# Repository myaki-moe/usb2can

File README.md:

# USB2CAN

USB2CAN is a compact and low cost open source USB to CAN bus adaptor. 

Based on candleLight firmware and STM32F072 crystal-less MCU, usb2can provides linux native socketcan support.

USB2CAN是一款紧凑且低成本的开源USB到CAN总线转化器.

基于candleLight固件和STM32F072无外置晶振MCU, usb2can提供了Linux原生SocketCAN支持.

## Quick Start | 快速开始

1. PCB proofing using GERBER file `usb2can_pcb/gerber/`
2. SMD or hand soldering using [ibom](usb2can_pcb/bom/ibom.html)
3. Build candleLight firmware
4. Flash the firmware using `dfu-utils`
5. Testing
```bash
sudo ip link set can0 up type can bitrate 1000000
# CAN receive
candump can0
# CAN send
cansend can0 200#5A5A5A5A5A5A5A5A
```

1. 使用GERBER文件 `usb2can_pcb/gerber/` 打样PCB
2. SMT或使用 [ibom](usb2can_pcb/bom/ibom.html)手工焊接
3. 编译candleLight固件
4. 使用 `dfu-utils` 烧录固件
5. 测试
```bash
sudo ip link set can0 up type can bitrate 1000000
# CAN receive
candump can0
# CAN send
cansend can0 200#5A5A5A5A5A5A5A5A
```

## Toolchains | 工具链

* PCB Design: KiCad 6.0.9
* Complier: arm-none-eabi-gcc 12.2.0
* Firmware Programmer: dfu-utils 0.11

* PCB设计: KiCad 6.0.9
* 编译器: arm-none-eabi-gcc 12.2.0
* 固件烧录: dfu-utils 0.11

## License | 许可证

* The USB2CAN project is released under GPLv3 license.

* candleLight Firmware Sources is distributed under the MIT License (MIT) Copyright (c) 2016 Hubert Denkmair

* The STM32 HAL is distributed under a non-restrictive BSD (Berkeley Software Distribution) license.

* Code from the STM32 USB library is licensed under ST STMicroelectronics [Ultimate Liberty license SLA0044](www.st.com/SLA0044)

* USB2CAN项目基于GPLv3协议发布

* candleLight固件源码根据MIT分发, 版权所有2016 Hubert Denkmair

* STM32 HAL 在非限制性BSD许可下分发.

* STM32 USB 库中的代码根据 [Ultimate Liberty license SLA0044](www.st.com/SLA0044) 获得许可

## Related Projects | 相关项目

[candleLight_fw](https://github.com/candle-usb/candleLight_fw)

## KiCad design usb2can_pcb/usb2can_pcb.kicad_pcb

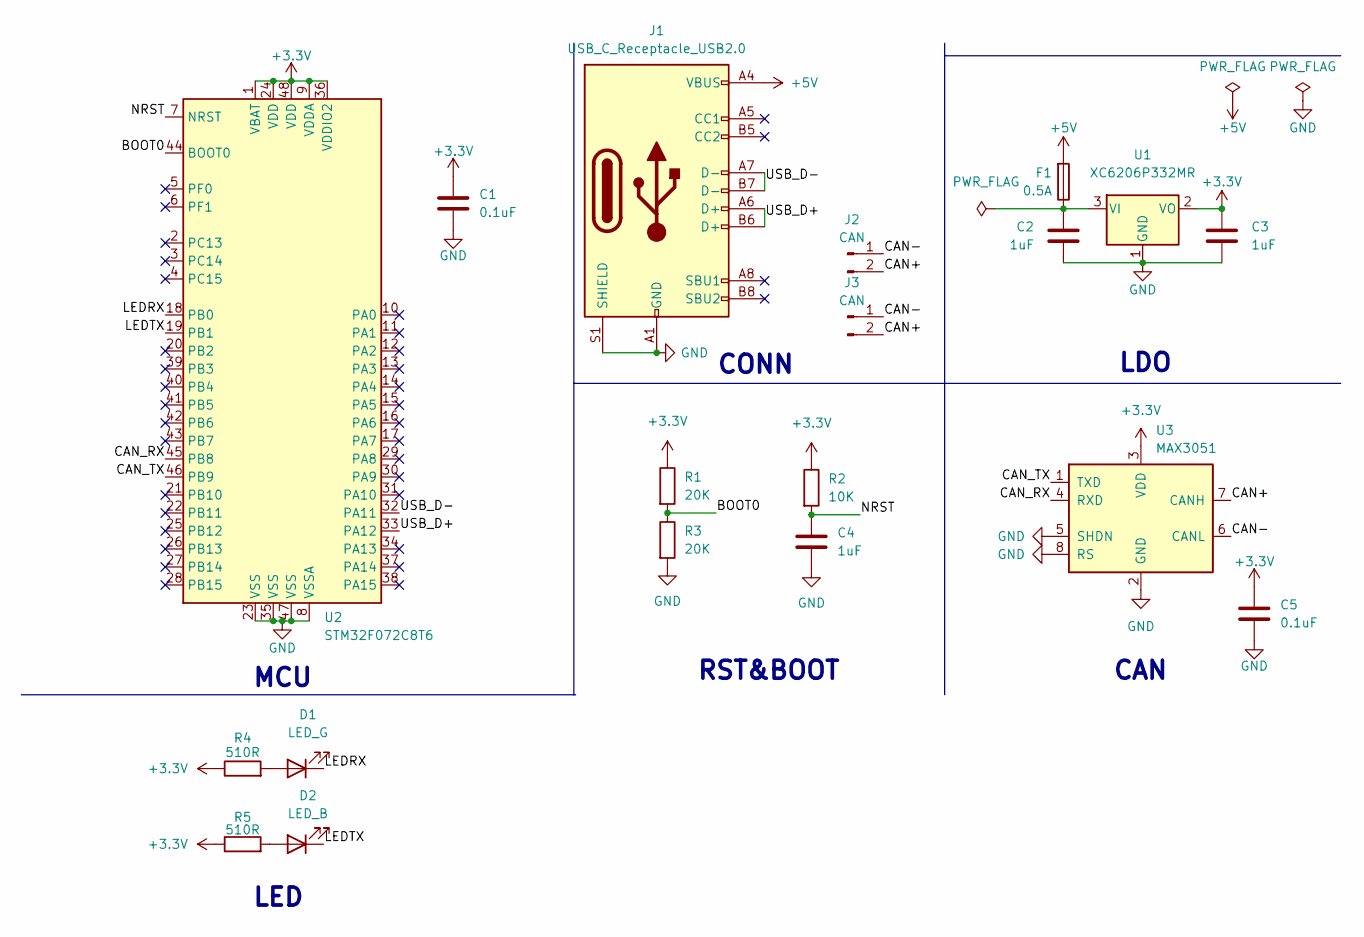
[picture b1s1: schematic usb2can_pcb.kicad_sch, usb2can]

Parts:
C1, C5: 0.1uF; C_0402_1005Metric
C2, C3, C4: 1uF; C_0402_1005Metric
D1: LED_G; D_0402_1005Metric
D2: LED_B; D_0402_1005Metric
F1: 0.5A; Fuse_0603_1608Metric
J1: USB_C_Receptacle_USB2.0; USB_C_Receptacle_Palconn_UTC16-G
J2, J3: CAN; JST_GH_SM02B-GHS-TB_1x02-1MP_P1.25mm_Horizontal
R1, R3: 20K; R_0402_1005Metric
R2: 10K; R_0402_1005Metric
R4, R5: 510R; R_0402_1005Metric
U1: XC6206P332MR; SOT-23
U2: STM32F072C8T6; LQFP-48_7x7mm_P0.5mm
U3: MAX3051; SOT-23-8

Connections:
+3.3V: C1.1, C3.1, C5.1, R1.1, R2.1, R4.1, R5.1, U1.2 (VO), U2.1 (VBAT), U2.9 (VDDA), U2.24 (VDD), U2.36 (VDDIO2), U2.48 (VDD), U3.3 (VDD)
+5V: F1.2, J1.A4 (VBUS), J1.A9 (VBUS), J1.B4 (VBUS), J1.B9 (VBUS)
/BOOT0: R1.2, R3.1, U2.44 (BOOT0)
/CAN+: J2.2, J3.2, U3.7 (CANH)
/CAN-: J2.1, J3.1, U3.6 (CANL)
/CAN_RX: U2.45 (PB8), U3.4 (RXD)
/CAN_TX: U2.46 (PB9), U3.1 (TXD)
/LEDRX: D1.1 (K), U2.18 (PB0)
/LEDTX: D2.1 (K), U2.19 (PB1)
/NRST: C4.1, R2.2, U2.7 (NRST)
/USB_D+: J1.A6 (D+), J1.B6 (D+), U2.33 (PA12)
/USB_D-: J1.A7 (D-), J1.B7 (D-), U2.32 (PA11)
GND: C1.2, C2.1, C3.2, C4.2, C5.2, J1.A1 (GND), J1.A12 (GND), J1.B1 (GND), J1.B12 (GND), J1.S1 (SHIELD), R3.2, U1.1 (GND), U2.8 (VSSA), U2.23 (VSS), U2.35 (VSS), U2.47 (VSS), U3.2 (GND), U3.5 (SHDN), U3.8 (RS)
unnamed: C2.2, F1.1, U1.3 (VI)
unnamed: D1.2 (A), R4.2
unnamed: D2.2 (A), R5.2

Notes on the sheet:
LED
RST&BOOT
CONN
CAN
LDO
MCU

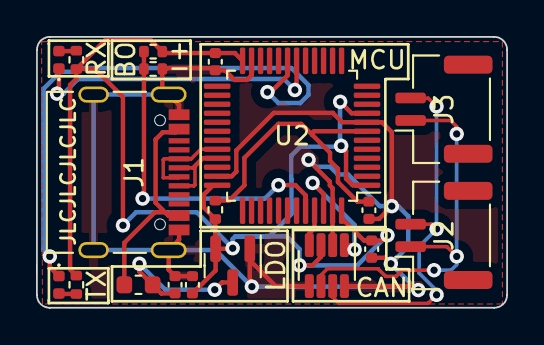
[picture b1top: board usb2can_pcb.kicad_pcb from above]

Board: 2 copper layers, 26.1 x 15.0 mm, 19 parts (0 on the bottom side), 16 nets.

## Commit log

2022-11-01 add candleLight firmware
2022-11-02 add pcb design 1.0
2022-11-02 add customer number placeholder for JLCPCB
2022-11-02 generate GERBER
2022-11-09 Generate interactive BOM
2022-11-09 add GPLv3 license
2022-11-09 add .gitattributes to fix repository statistics error
2022-11-10 fix CAN connector pin assign problem
2022-11-12 fix sch version display error
2022-11-12 fix pcb version display error
2023-01-23 doc: update chinese ver
